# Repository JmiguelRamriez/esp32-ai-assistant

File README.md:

# Asistente Inteligente IA con ESP32 🤖

Un asistente de voz autónomo basado en hardware ESP32 que utiliza la potencia de la nube (Flask + Groq) para mantener conversaciones fluidas. "Luna" es capaz de escuchar tus peticiones, procesar transcripciones ultrarrápidas, generar inteligencia conversacional con Llama-3.1 y responder con voz de forma directa por sus altavoces, a la vez que muestra animaciones en su pantalla OLED interactiva.

---

## Características Principales

1. **Interacción Dual**:
   - **Wake Word ("Luna")**: Escucha continua optimizada. Puedes llamarla por su nombre, el ESP32 transmite al backend para confirmar la detección y despierta de inmediato.
   - **Botón Físico**: Interacción clásica manteniendo presionado un pulsador (Pin 14) para dictar o grabar peticiones manualmente.
2. **Sistema VAD (Voice Activity Detection)**:
   - Implementado nativamente en MicroPython local. La grabación para la detección de la palabra de activación se dispara solo si la amplitud del micrófono supera un umbral dinámico (se evitan grabaciones en silencio), ahorrando batería y ancho de banda al servidor.
3. **Gestión de Red y Memoria Avanzada**:
   - **Sockets HTTP Manuales y Chunking**: Para evitar los severos límites de RAM en MicroPython al enviar archivos pesados (WAVs completos), el cliente usa sockets HTTP puros y _chunking_ (envío múltiple fragmentado del búfer).
   - **Auto-Estabilización WiFi**: El controlador de red local cuenta con reinicio lógico forzoso, sorteando con solidez los conocidos bloqueos de conexión fantasma en los ESP32.
4. **Reproducción Estabilizada por Hardware DAC**:
   - **Audio Puro**: El backend construye respuestas TTS de pydub a formato PCM 8000Hz Mono, de 8-bits unsigned. Formato nativo para el DAC del ESP32 (Pines 25 y 26).
   - **Compensación de Latencia**: El bucle de lectura/escritura en MicroPython tiene retrasos medidos y deducidos del Sample Rate original usando compensación en microsegundos, asegurando máxima sincronía y evitando saltos de audio.
5. **Interfaz Visual Viva (Pantalla SH1106)**:
   - Pantalla interactiva que reacciona según cada fase del pipeline (dormido/Zzzz, sorprendido al escuchar, cargando mientras procesa la red, hablando al transcribir, u ojos tristes si surge algún fallo).
   - Reloj local mantenido en segundo plano gracias a sincronización remota por NTP (Network Time Protocol).
6. **Backend Potenciado por IA de Groq**:
   - `/transcribir` y `/despertar` delegan el audio recogido hacia **Whisper Large V3 Turbo** de Groq.
   - `/preguntar` redirige el texto al modelo **Llama-3.1-8B-Instant**, incorporando el archivo `historial.json` para gestionar un contexto temporal configurable.
   - "Miguel" es el pre-prompt. Una personalidad de universitario, 20 años que es amable y precisa.

---

## Arquitectura del Sistema

El ecosistema consiste en un modelo "Cliente Front" (ESP32) y un "Servidor de Carga" (Python Flask):

```text
Asistente/
├── firmware/                 # CÓDIGO MICROPYTHON PARA EL ESP32 (SUBIR A LA PLACA)
│   ├── main.py               # Máquina de estados: Ciclo de Pooling de botones/micrófono y manejo visual UI.
│   ├── config.py             # Archivo para inyección de credenciales WiFi y dirección IP/Host.
│   ├── cliente.py            # Orquestador de peticiones: streaming de audios usando *usocket* crudo.
│   ├── grabar.py             # Control I2S (RX) del micrófono, lectura en bloques y aplicación de algoritmo VAD.
│   ├── reproductor.py        # Salida analógica. Lee un .wav y lo transfiere a los pines DAC ciclo por ciclo.
│   ├── pantalla.py           # Gestor gráfico (I2C): rendering frame-a-frame de las expresiones faciales.
│   ├── sh1106.py             # Controlador de hardware display monocromo, primitivas gráficas nativas.
│   └── wifi.py               # Boot de red confiable (Auto-reconexión profunda de interfaces STA).
│
├── firmware/servidor/        # BACKEND FLASK (En tu computadora local o la nube (PaaS / Render))
│   ├── servidor.py           # Expone API: /transcribir, /preguntar, /hablar, /despertar, /reset.
│   ├── requirements.txt      # Paquetes a instalar con pip (flask, requests, gtts, pydub, python-dotenv).
│   └── (historial.json)      # Fichero de base de datos auto-regenerado con memoria de largo plazo.
│
└── hardware/                 # RECURSOS FÍSICOS
    └── Asistente.kicad_pro   # Archivos de diagramas, ruteos (PCB layouts) provistos en formato KiCAD.
```

---

## Entradas y Salidas de Hardware (Diagrama Lógico Base)

- **Placa Principal**: Microcontrolador ESP32 (Se prefiere modelo clásico ESP-WROOM-32 estándar para aprovechar los 2 pines DAC).
- **Entrada de Audio (Micrófono I2S como INMP441)**:
  - SCK -> Pin 32
  - WS -> Pin 27
  - SD -> Pin 33
- **Salida de Pantalla (Pantalla OLED 1.3" I2C)**:
  - SCL -> Pin 22
  - SDA -> Pin 21
- **Salida de Audio Principal (DAC x2)**:
  - Canal L (Izquierdo) -> Pin 25 a la entrada analógica del circuito amplificador (Ej: PAM8403 / LM386).
  - Canal R (Derecho) -> Pin 26 a la entrada del ampli (o bocina / audífonos si se está derivando).
- **Control**:
  - Un pulsador general unido a un Pin de señal en Pull-Up conectado directo a -> Pin 14.

### Esquemático y Diseño PCB

---

## Instalación y Despliegue

### 1. Levantar el Backend / Cerebro en Flask

Es indispensable correr este código de la carpeta en algún entorno de gran capacidad de procesamiento (Tu PC, o Render.com). Se requiere tener **FFmpeg** instalado a nivel sistema operativo para que la librería PyDub trabaje adecuadamente los archivos de sonido Gtts hacia `.wav` genérico.

1. Abre tu terminal y ve al sistema de archivos a `firmware/servidor`.
2. Instala las dependencias de control: `pip install -r requirements.txt`.
3. Crea a mano un fichero `.env` y dale permisos añadiendo tu API de procesamiento: `GROQ_API_KEY=tu_clave_de_api_aqui`.
4. Corre el cerebro local: `python servidor.py` (Dejalo encendido, escuchará en `http://0.0.0.0:5000`).

### 2. Flashear el Firmware MicroPython en el ESP32

1. Previamente graba el firmware _MicroPython_ (versión 1.19+ recomendada) en tu ESP32 con herramientas como Thonny IDE.
2. Mantén Abierto Thonny IDE. Modifica `firmware/config.py` e ingresa tu:
   - Red Inalámbrica `SSID` y de `PASSWORD` local de la habitación.
   - El hostname del servidor maestro y su puerto. Ejemplo: Para tu computadora bajo local WiFi usa la IP `SERVIDOR = "192.168.1.XX" y PUERTO = 5000`. Si usas dominio real SSL usa `PUERTO = 443`.
3. Arrastra a la memoria base del ESP32 `/` todos los ficheros .py de la carpeta principal del firmware.
4. Presiona RST/EN en la física placa del ESP (Hard-Reset). La placa reiniciará, te dirá que hace ping al NTP, y abrirá los ojos preparándose para funcionar.

### Ciclo de Uso:

1. **Atención**: Acercate a su micrófono y di "Luna" con voz clara (o si lo prefieres, pulsa y sosten tu botón durante 3 segundos al hablar).
2. **Sorpresa**: La pantallita de OLED abrirá los ojos grande y te indicará por serial "Escuchando...". Pídele que elabore algún tema académico o una definición rápida.
3. **Caché**: El modelo cambiará a "carita dudando a los lados" y en breves momentos, el generador LLaMA 3.1 descargará de un tazón el WAV procesado.
4. **Respuesta**: El ESP32 se enlazará localmente de hardware y su bocina hablará mientras simula de forma fluida y divertida ondas de palabras. ¡Listo!

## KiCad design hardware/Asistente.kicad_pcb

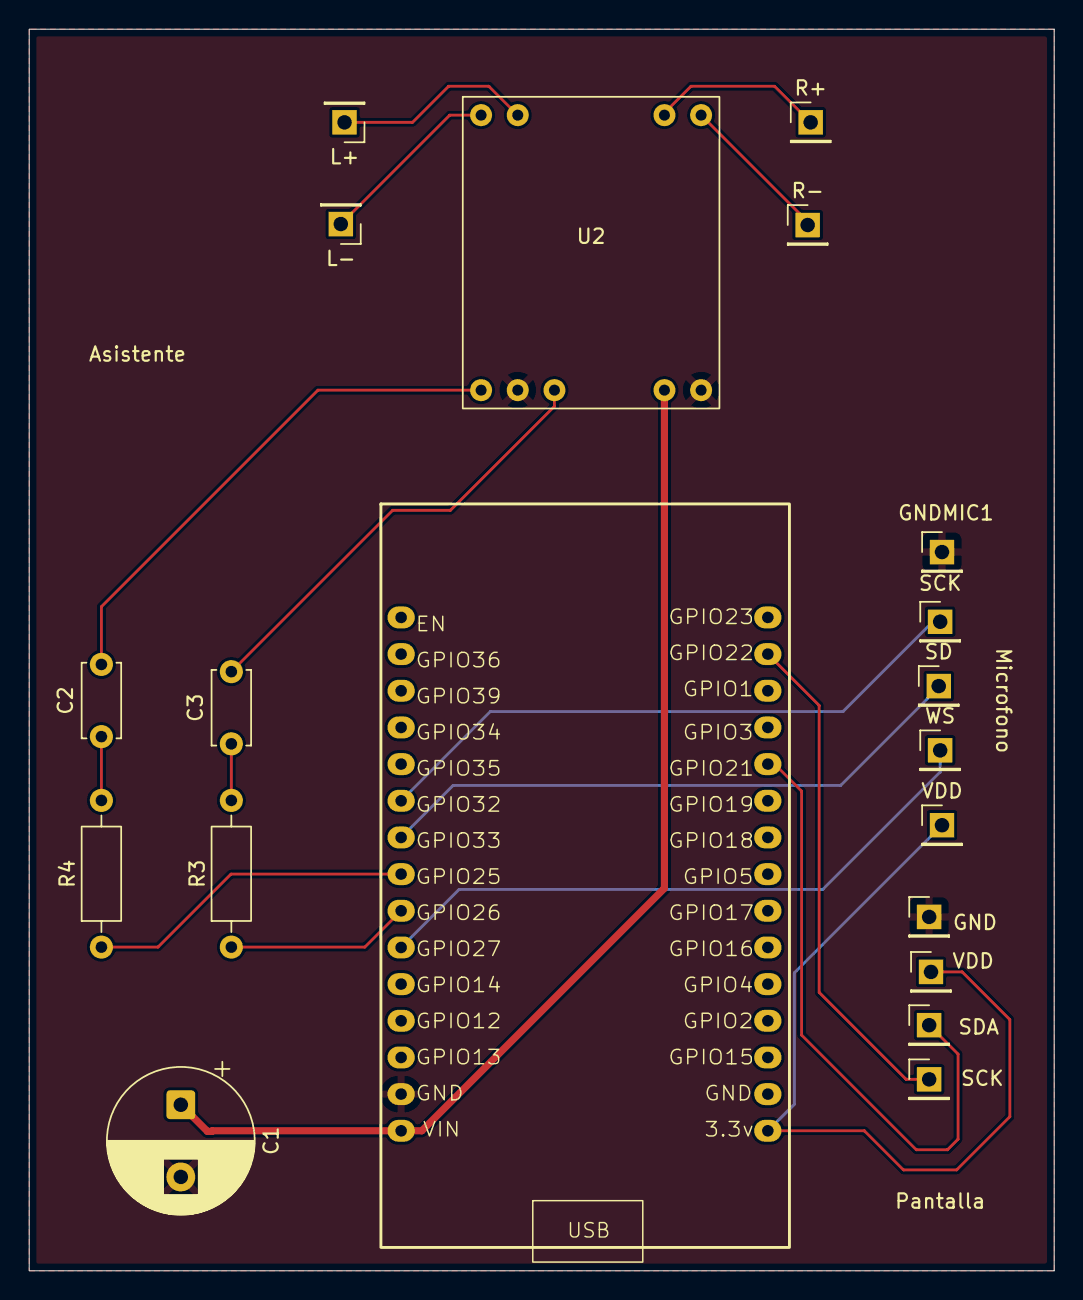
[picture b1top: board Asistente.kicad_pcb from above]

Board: 2 copper layers, 71.0 x 86.0 mm, 20 parts (0 on the bottom side), 18 nets.

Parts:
C1: 1000uF; CP_Radial_D10.0mm_P5.00mm
C2, C3: 100nf; C_Disc_D5.0mm_W2.5mm_P5.00mm
GND: Conn_01x01_Pin; PinHeader_1x01_P2.54mm_Vertical
GNDMIC1: Conn_01x01_Pin; PinHeader_1x01_P2.54mm_Vertical
L+: Conn_01x01_Pin; PinHeader_1x01_P2.54mm_Vertical
L-: Conn_01x01_Pin; PinHeader_1x01_P2.54mm_Vertical
R3, R4: 1k; R_Axial_DIN0207_L6.3mm_D2.5mm_P10.16mm_Horizontal
R+: Conn_01x01_Pin; PinHeader_1x01_P2.54mm_Vertical
R-: Conn_01x01_Pin; PinHeader_1x01_P2.54mm_Vertical
SCK: Conn_01x01_Pin; PinHeader_1x01_P2.54mm_Vertical
SCK#2: Conn_01x01_Pin; PinHeader_1x01_P2.54mm_Vertical
SD: Conn_01x01_Pin; PinHeader_1x01_P2.54mm_Vertical
SDA: Conn_01x01_Pin; PinHeader_1x01_P2.54mm_Vertical
U1: ESP32_30pin
U2: pam8403
VDD: Conn_01x01_Pin; PinHeader_1x01_P2.54mm_Vertical
VDD#2: Conn_01x01_Pin; PinHeader_1x01_P2.54mm_Vertical
WS: Conn_01x01_Pin; PinHeader_1x01_P2.54mm_Vertical

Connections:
+5V: C1.1, U1.1 (VIN), U2.4 (vin)
GND: C1.2, GND.1, GNDMIC1.1, U1.2 (GND), U2.2 (T), U2.5 (gnd)
unnamed: C2.1, R4.2
unnamed: C3.1, R3.2
unnamed: SCK#2.1, U1.29 (GPIO22)
unnamed: SDA.1, U1.26 (GPIO21)
unnamed: U1.16 (3.3v), VDD.1, VDD#2.1
unnamed: L-.1, U2.9 (L-)
unnamed: L+.1, U2.8 (L+)
unnamed: R-.1, U2.6 (R-)
unnamed: R+.1, U2.7 (R+)
unnamed: SD.1, U1.9 (GPIO33)
unnamed: SCK.1, U1.10 (GPIO32)
unnamed: U1.6 (GPIO27), WS.1
unnamed: R4.1, U1.8 (GPIO25)
unnamed: R3.1, U1.7 (GPIO26)
unnamed: C2.2, U2.1 (L)
unnamed: C3.2, U2.3 (R)

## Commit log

2026-03-16 add gitnore
2026-03-17 add wifi
2026-03-18 Add ia
2026-03-18 Add mic, and ia
2026-03-18 Remove hardcoded API key, add .env
2026-03-18 functional voice assistant with ESP32, AI, and OLED animations
2026-03-19 Add folder server
2026-03-19 Add speakers
2026-03-19 Add runtime to requirements
2026-03-19 Update requirements
2026-03-19 Update cliente
2026-03-19 Update cliente and servidor
2026-03-19 functional ai assistant and server
2026-03-19 fix: resolve hardware conflicts and JSON encoding issues
2026-03-19 docs: add comprehensive README with architecture, BOM and setup guide
2026-03-19 feat: improve OLED animations and document entire project
2026-03-22 Corrige indentación en endpoint /despertar y agrega tolerancia al wake word
2026-03-22 Fix wake word threshold in main.py, remove blocking loop in grabar.py, and add transcription tolerance in servidor.py
2026-03-22 Limpieza: remueve archivos temporales y codigo obsoleto
2026-03-22 Fix module attribute error by forcing cliente.py sync and enable full wake word interaction
2026-03-23 docs: update README with wake word feature and backend endpoints
2026-03-23 hw: update PCB layout, add Gerber files and INMP441 footprint
2026-03-23 feat: implement WDT, timeouts, WiFi reconnect, OLED indicators and volume norm
2026-03-23 Fix wake word detection: add pre-roll buffer, adjust VAD threshold, and improve Whisper prompting
2026-03-27 feat: add external connectors for OLED, mic and speakers, update gerber files
2026-03-27 docs: add schematic and PCB images
2026-03-27 docs: rewrite README to comprehensively document project architecture and hardware
2026-03-30 Refactor and remove obsolete files
